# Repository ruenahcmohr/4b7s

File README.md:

# 4b7s
a 4 bit 7 segment decoder, super simple, but not BCD!

The story is (was when I left it) at 
 https://hackaday.io/page/21308-the-7-segment-decoder-done-wrong

All the files you should need to send off to have them made are in
the gerber directory. I'm sorry there was no room for slikscreens :]

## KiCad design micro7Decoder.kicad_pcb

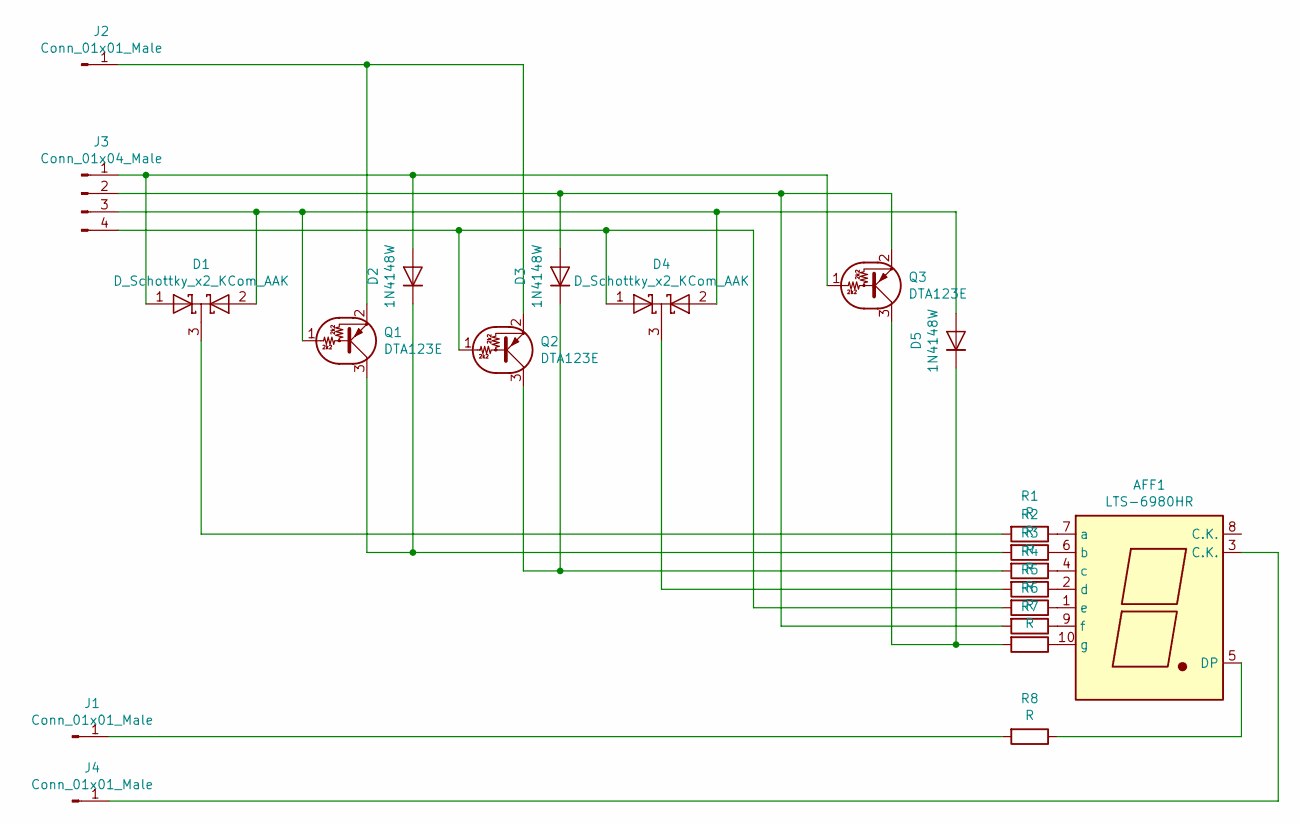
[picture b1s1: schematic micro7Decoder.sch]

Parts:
AFF1: LTS-6980HR; 7SegmentLED_LTS6760_LTS6780
D1, D4: D_Schottky_x2_KCom_AAK; SOT-23
D2, D3, D5: 1N4148W; D_SOT-23_ANK
J1, J2, J4: Conn_01x01_Male; PinHeader_1x01_P2.54mm_Vertical
J3: Conn_01x04_Male; PinHeader_1x04_P2.54mm_Vertical
Q1, Q2, Q3: DTA123E; SOT-23
R1, R2, R3, R4, R5, R6, R7, R8: R; R_0805_2012Metric_Pad1.15x1.40mm_HandSolder

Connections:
unnamed: AFF1.1 (e), R5.1
unnamed: AFF1.2 (d), R4.1
unnamed: AFF1.3 (C.K.), J4.1
unnamed: AFF1.4 (c), R3.1
unnamed: AFF1.5 (DP), R8.1
unnamed: AFF1.6 (b), R2.1
unnamed: AFF1.7 (a), R1.1
unnamed: AFF1.9 (f), R6.1
unnamed: AFF1.10 (g), R7.1
unnamed: D1.1 (A), D2.2 (A), J3.1, Q3.1 (B)
unnamed: D1.2 (A), D4.2 (A), D5.2 (A), J3.3, Q1.1 (B)
unnamed: D1.3 (K), R1.2
unnamed: D2.1 (K), Q1.3 (C), R2.2
unnamed: D3.1 (K), Q2.3 (C), R3.2
unnamed: D3.2 (A), J3.2, Q3.2 (E), R6.2
unnamed: D4.1 (A), J3.4, Q2.1 (B), R5.2
unnamed: D4.3 (K), R4.2
unnamed: D5.1 (K), Q3.3 (C), R7.2
unnamed: J1.1, R8.2
unnamed: J2.1, Q1.2 (E), Q2.2 (E)

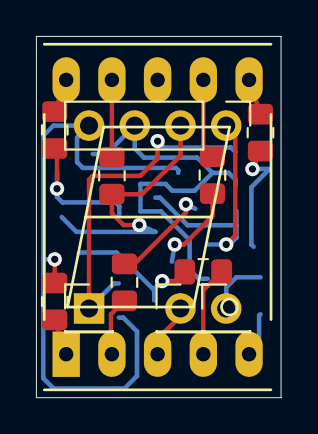
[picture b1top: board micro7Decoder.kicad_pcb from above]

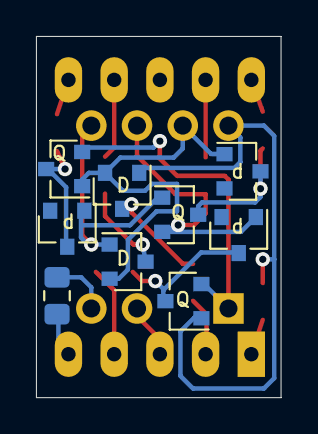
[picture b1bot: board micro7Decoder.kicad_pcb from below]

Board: 2 copper layers, 13.6 x 20.1 mm, 21 parts (9 on the bottom side), 20 nets.

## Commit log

2024-08-22 adding files
